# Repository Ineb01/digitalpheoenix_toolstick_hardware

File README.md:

# Digitalphoenix Toolstick
This repository includes the KiCad project files for the Digitalphenix Toolstick

## Clone
If you want to clone this repository it is important to clone it with all submodules e.g. 

`git clone --recurse-submodules https://github.com/Ineb01/digitalphoenix_toolstick_hardware.git`

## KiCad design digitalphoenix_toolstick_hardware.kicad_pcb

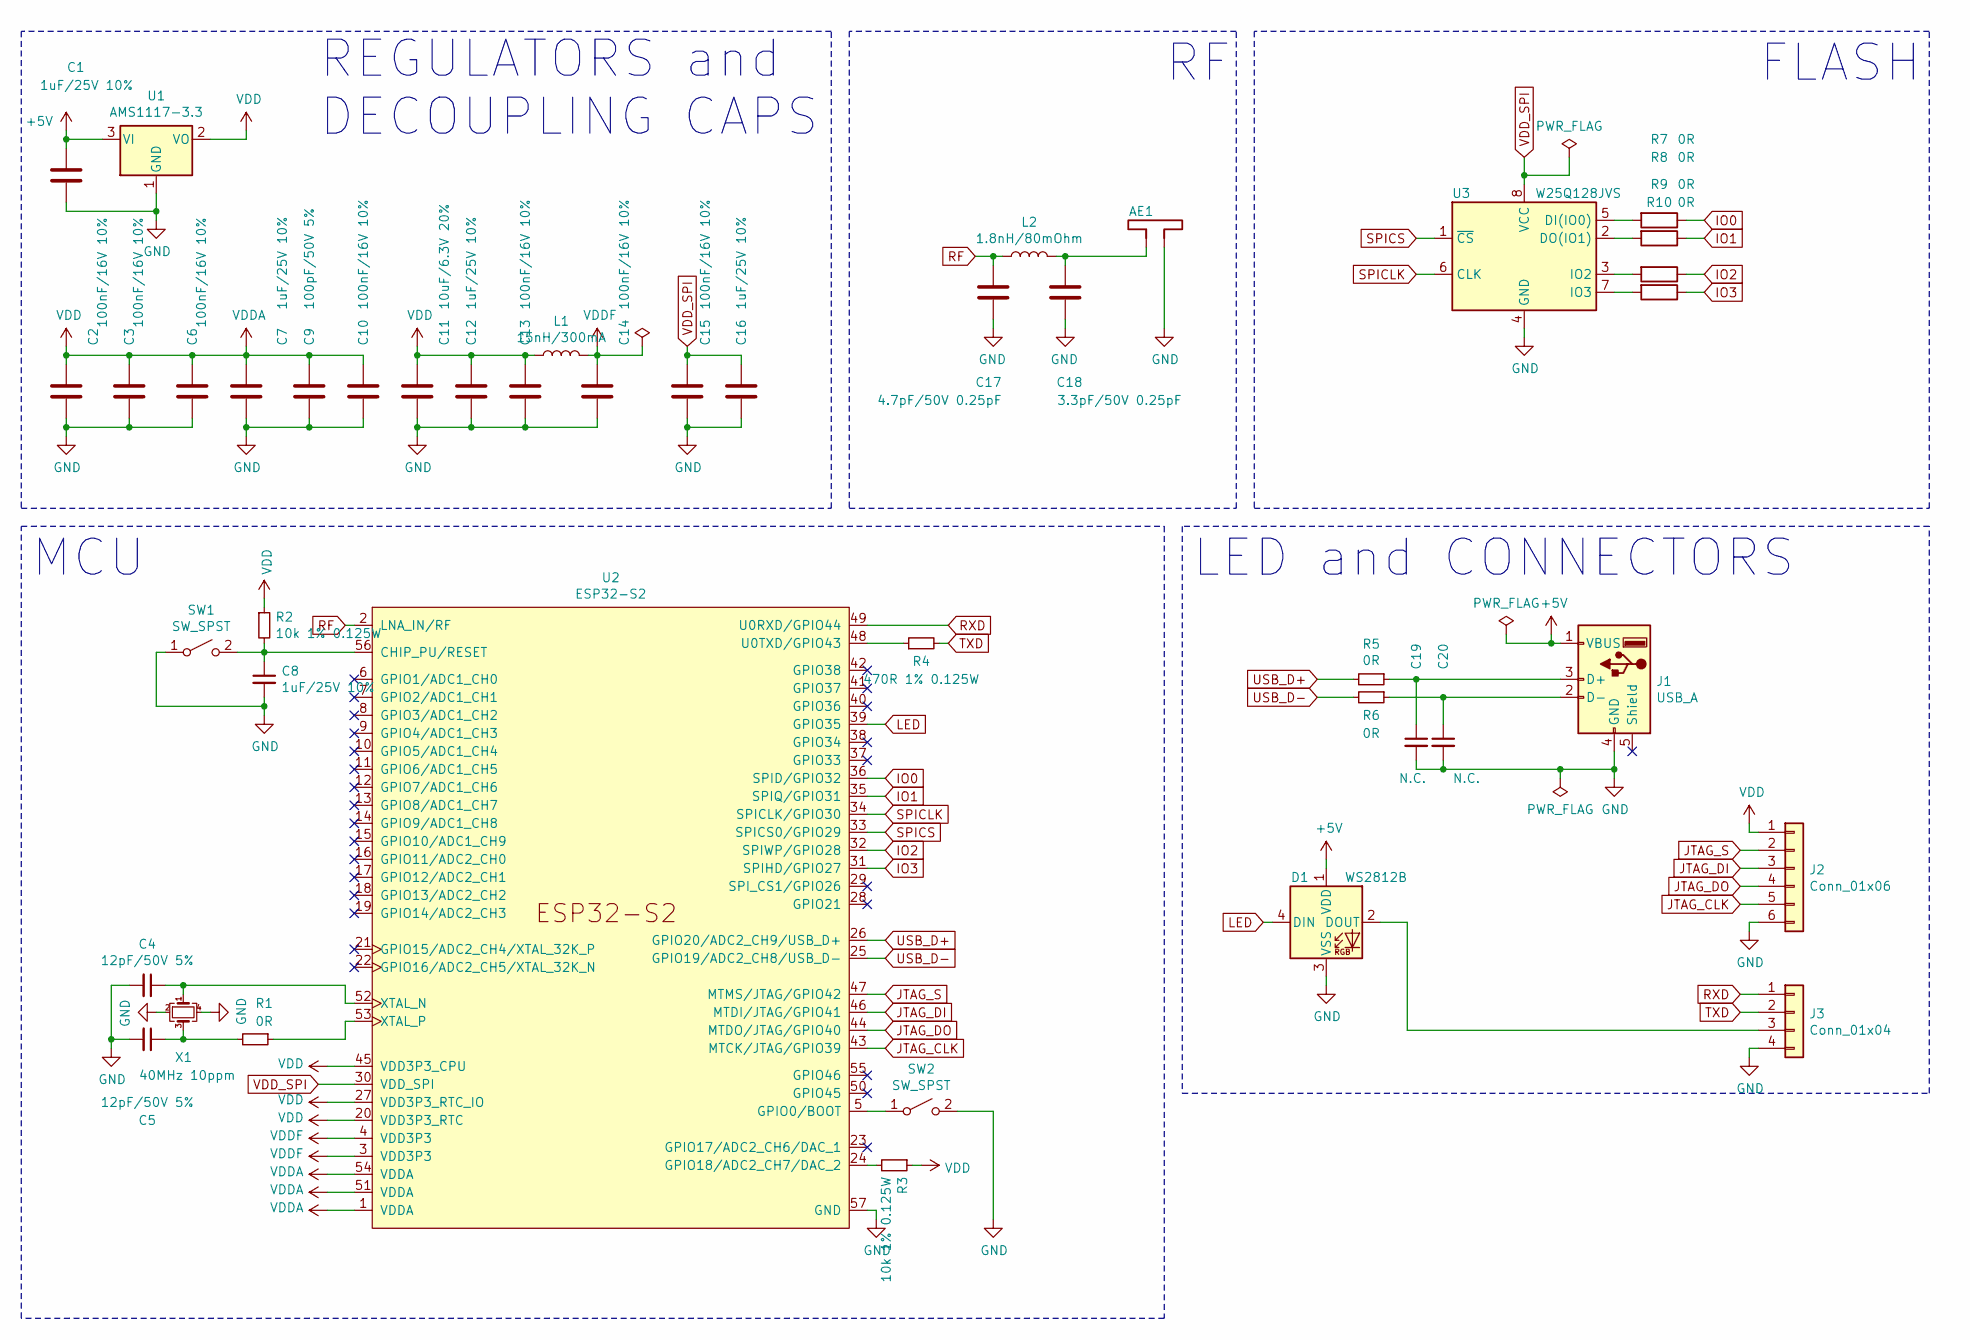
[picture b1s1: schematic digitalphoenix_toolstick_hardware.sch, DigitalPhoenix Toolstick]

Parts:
AE1: 2.4GHz 50R Antenna; Texas_SWRA117D_2.4GHz_Left
C1, C7, C8, C12, C16: 1uF/25V 10%; C_0402_1005Metric; LCSC_Number C52923
C2, C3, C6, C10, C13, C14, C15: 100nF/16V 10%; C_0402_1005Metric; LCSC_Number C1525
C4, C5: 12pF/50V 5%; C_0402_1005Metric; LCSC_Number C1547
C9: 100pF/50V 5%; C_0402_1005Metric; LCSC_Number C1547
C11: 10uF/6.3V 20%; C_0402_1005Metric; LCSC_Number C15525
C17: 4.7pF/50V 0.25pF; C_0402_1005Metric; LCSC_Number C1569
C18: 3.3pF/50V 0.25pF; C_0402_1005Metric; LCSC_Number C1565
C19, C20: N.C.; C_0402_1005Metric
D1: WS2812B; LED_WS2812B_PLCC4_5.0x5.0mm_P3.2mm; LCSC_Number C2890364
J1: USB_A; CONN-USB-A-PCB-TRACES
J2: Conn_01x06; PinSocket_1x06_P2.54mm_Vertical
J3: Conn_01x04; PinSocket_1x04_P2.54mm_Vertical
L1: 15nH/300mA; L_0402_1005Metric; LCSC_Number C27143
L2: 1.8nH/80mOhm; L_0402_1005Metric; LCSC_Number C77107
R1, R5, R6, R7, R8, R9, R10: 0R; R_0402_1005Metric; LCSC_Number C17168
R2, R3: 10k 1% 0.125W; R_0402_1005Metric; LCSC_Number C25744
R4: 470R 1% 0.125W; R_0402_1005Metric; LCSC_Number C25117
SW1, SW2: SW_SPST; SW_Push_SPST_NO_Alps_SKRK; LCSC_Number C455280
U1: AMS1117-3.3; SOT-223-3_TabPin2; LCSC_Number C6186
U2: ESP32-S2; QFN-56-1EP_7x7mm_P0.4mm_EP5.6x5.6mm; LCSC_Number C529594
U3: W25Q128JVS; SOIC-8_5.23x5.23mm_P1.27mm; LCSC_Number C97521
X1: 40MHz 10ppm; Crystal_SMD_3225-4Pin_3.2x2.5mm; LCSC_Number C90924

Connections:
+5V: C1.1, D1.1 (VDD), J1.1 (VBUS), U1.3 (VI)
GND: AE1.2, C1.2, C2.2, C3.2, C4.2, C5.2, C6.2, C7.2, C8.2, C9.2, C10.2, C11.2, C12.2, C13.2, C14.2, C15.2, C16.2, C17.2, C18.2, C19.2, C20.2, D1.3 (VSS), J1.4 (GND), J2.6, J3.4, SW1.1 (A), SW2.2 (B), U1.1 (GND), U2.57 (GND), U3.4 (GND), X1.2, X1.4
IO0: R7.1, U2.36 (SPID/GPIO32)
IO1: R8.1, U2.35 (SPIQ/GPIO31)
IO2: R9.1, U2.32 (SPIWP/GPIO28)
IO3: R10.1, U2.31 (SPIHD/GPIO27)
JTAG_CLK: J2.5, U2.43 (MTCK/JTAG/GPIO39)
JTAG_DI: J2.3, U2.46 (MTDI/JTAG/GPIO41)
JTAG_DO: J2.4, U2.44 (MTDO/JTAG/GPIO40)
JTAG_S: J2.2, U2.47 (MTMS/JTAG/GPIO42)
LED: D1.4 (DIN), U2.39 (GPIO35)
unnamed: AE1.1, C18.1, L2.2
unnamed: C4.1, U2.52 (XTAL_N), X1.1
unnamed: C5.1, R1.2, X1.3
unnamed: C8.1, R2.2, SW1.2 (B), U2.56 (CHIP_PU/RESET)
unnamed: C19.1, J1.3 (D+), R5.1
unnamed: C20.1, J1.2 (D-), R6.1
unnamed: D1.2 (DOUT), J3.3
unnamed: R1.1, U2.53 (XTAL_P)
unnamed: R3.2, U2.24 (GPIO18/ADC2_CH7/DAC_2)
unnamed: R4.1, U2.48 (U0TXD/GPIO43)
unnamed: R7.2, U3.5 (DI(IO0))
unnamed: R8.2, U3.2 (DO(IO1))
unnamed: R9.2, U3.3 (IO2)
unnamed: R10.2, U3.7 (IO3)
unnamed: SW2.1 (A), U2.5 (GPIO0/BOOT)
RF: C17.1, L2.1, U2.2 (LNA_IN/RF)
RXD: J3.1, U2.49 (U0RXD/GPIO44)
SPICLK: U2.34 (SPICLK/GPIO30), U3.6 (CLK)
SPICS: U2.33 (SPICS0/GPIO29), U3.1 (~CS)
TXD: J3.2, R4.2
USB_D+: R5.2, U2.26 (GPIO20/ADC2_CH9/USB_D+)
USB_D-: R6.2, U2.25 (GPIO19/ADC2_CH8/USB_D-)
VDD: C2.1, C3.1, C6.1, C7.1, C9.1, C10.1, C11.1, C12.1, C13.1, J2.1, L1.1, R2.1, R3.1, U1.2 (VO), U2.1 (VDDA), U2.20 (VDD3P3_RTC), U2.27 (VDD3P3_RTC_IO), U2.45 (VDD3P3_CPU), U2.51 (VDDA), U2.54 (VDDA)
VDDF: C14.1, L1.2, U2.3 (VDD3P3), U2.4 (VDD3P3)
VDD_SPI: C15.1, C16.1, U2.30 (VDD_SPI), U3.8 (VCC)

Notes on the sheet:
REGULATORS and DECOUPLING CAPS
FLASH
MCU
LED and CONNECTORS

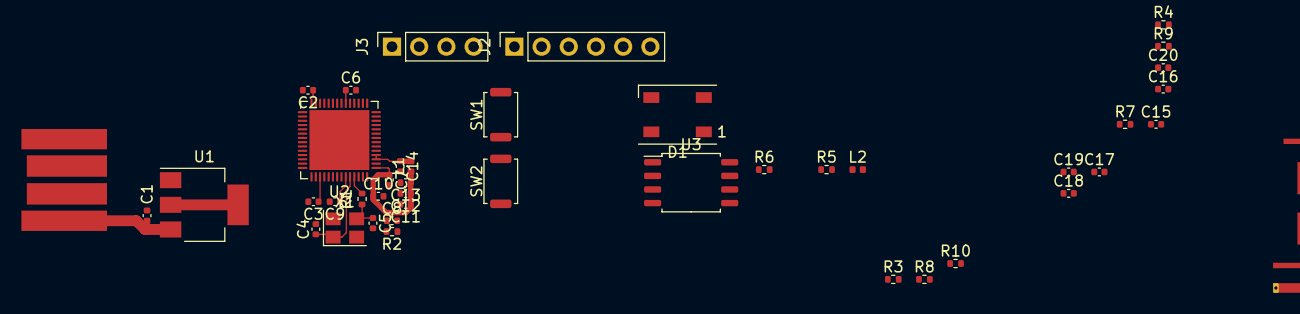
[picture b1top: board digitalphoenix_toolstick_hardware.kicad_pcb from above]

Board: 2 copper layers, 43 parts (0 on the bottom side), 36 nets.

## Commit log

2021-12-06 Add License GPLv3
2021-12-06 Added Espressif KiCad libraries
2021-12-06 Add libraries to project lib-table
2021-12-06 Basic schematic. unfinished for now
2021-12-06 Working on V0.1 Schematic
2021-12-06 Removed bak file
2021-12-07 Footprints and starting the PCB
2021-12-07 More PCB work
